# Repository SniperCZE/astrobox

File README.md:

# astrobox
DJ mixpult for amateur astronomy

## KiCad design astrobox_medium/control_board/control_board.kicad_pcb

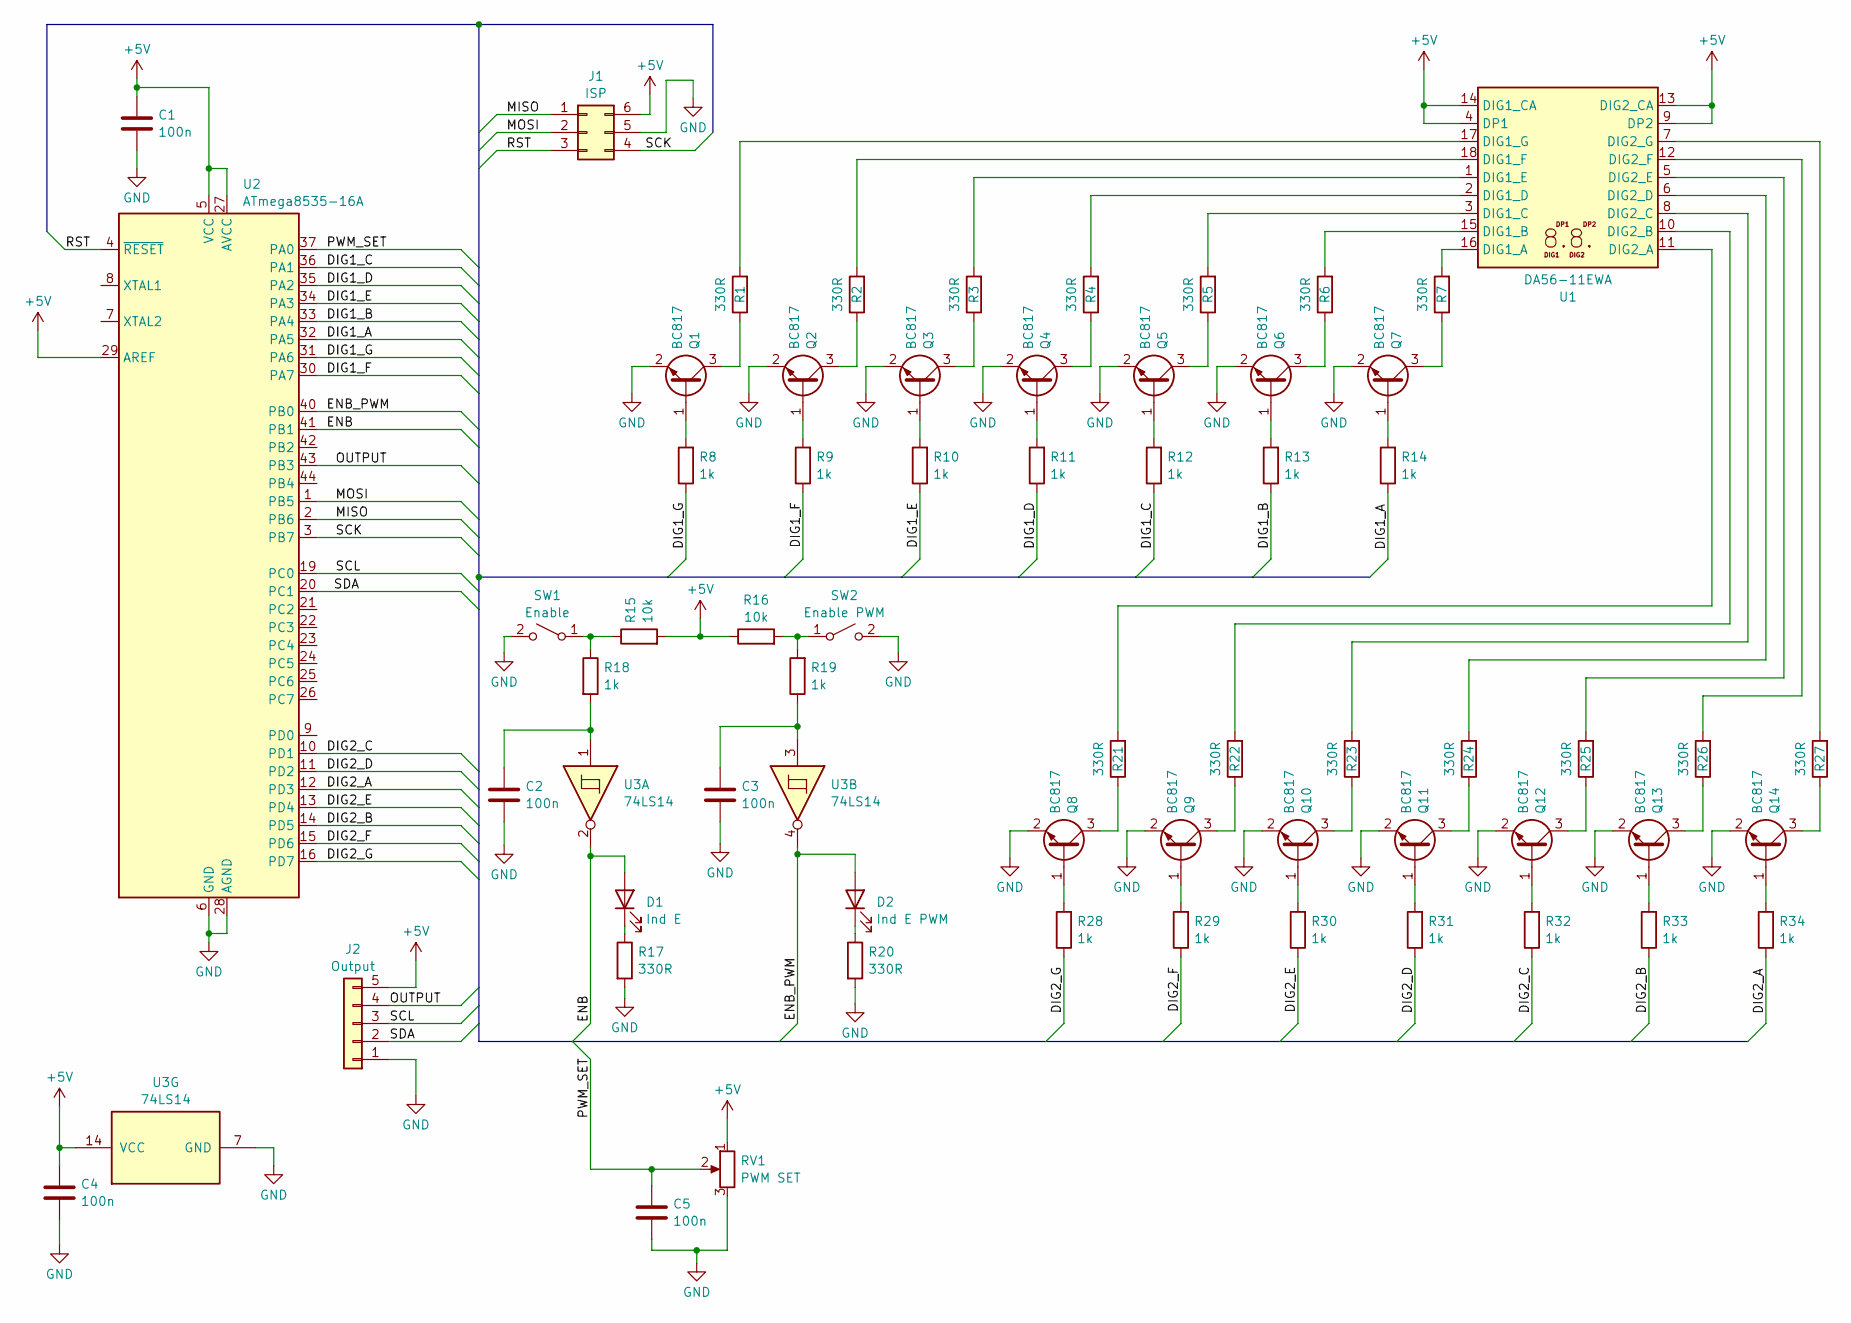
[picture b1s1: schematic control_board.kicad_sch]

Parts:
C1, C2, C3, C4, C5: 100n; C_1206_3216Metric_Pad1.33x1.80mm_HandSolder
D1: Ind E; LED_D5.0mm
D2: Ind E PWM; LED_D5.0mm
J1: ISP; PinHeader_2x03_P2.54mm_Vertical
J2: Output; SolderWire-1.5sqmm_1x05_P6mm_D1.7mm_OD3mm
Q1, Q2, Q3, Q4, Q5, Q6, Q7, Q8, Q9, Q10, Q11, Q12, Q13, Q14: BC817; SOT-23
R1, R2, R3, R4, R5, R6, R7, R17, R20, R21, R22, R23, R24, R25, R26, R27: 330R; R_1206_3216Metric_Pad1.30x1.75mm_HandSolder
R8, R9, R10, R11, R12, R13, R14, R18, R19, R28, R29, R30, R31, R32, R33, R34: 1k; R_1206_3216Metric_Pad1.30x1.75mm_HandSolder
R15, R16: 10k; R_1206_3216Metric_Pad1.30x1.75mm_HandSolder
RV1: PWM SET; SolderWire-1sqmm_1x03_P5.4mm_D1.4mm_OD2.7mm
SW1: Enable; SolderWire-1sqmm_1x02_P5.4mm_D1.4mm_OD2.7mm
SW2: Enable PWM; SolderWire-1sqmm_1x02_P5.4mm_D1.4mm_OD2.7mm
U1: DA56-11EWA; DA56-11SURKWA
U2: ATmega8535-16A; TQFP-44_10x10mm_P0.8mm
U3: 74LS14; SO-14_3.9x8.65mm_P1.27mm

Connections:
+5V: C1.1, C4.1, J1.6, J2.5, R15.2, R16.1, RV1.1, U1.4 (DP1), U1.9 (DP2), U1.13 (DIG2_CA), U1.14 (DIG1_CA), U2.5 (VCC), U2.17 (VCC), U2.27 (AVCC), U2.29 (AREF), U2.38 (VCC), U3.14 (VCC)
/DIG1_A: R14.1, U2.32 (PA5)
/DIG1_B: R13.1, U2.33 (PA4)
/DIG1_C: R12.1, U2.36 (PA1)
/DIG1_D: R11.1, U2.35 (PA2)
/DIG1_E: R10.1, U2.34 (PA3)
/DIG1_F: R9.1, U2.30 (PA7)
/DIG1_G: R8.1, U2.31 (PA6)
/DIG2_A: R34.1, U2.12 (PD3)
/DIG2_B: R33.1, U2.14 (PD5)
/DIG2_C: R32.1, U2.10 (PD1)
/DIG2_D: R31.1, U2.11 (PD2)
/DIG2_E: R30.1, U2.13 (PD4)
/DIG2_F: R29.1, U2.15 (PD6)
/DIG2_G: R28.1, U2.16 (PD7)
/ENB: D1.2 (A), U2.41 (PB1), U3.2
/ENB_PWM: D2.2 (A), U2.40 (PB0), U3.4
/MISO: J1.1, U2.2 (PB6)
/MOSI: J1.2, U2.1 (PB5)
/OUTPUT: J2.4, U2.43 (PB3)
/PWM_SET: C5.1, RV1.2, U2.37 (PA0)
/RST: J1.3, U2.4 (~RESET)
/SCK: J1.4, U2.3 (PB7)
/SCL: J2.3, U2.19 (PC0)
/SDA: J2.2, U2.20 (PC1)
GND: C1.2, C2.2, C3.2, C4.2, C5.2, J1.5, J2.1, Q1.2 (E), Q2.2 (E), Q3.2 (E), Q4.2 (E), Q5.2 (E), Q6.2 (E), Q7.2 (E), Q8.2 (E), Q9.2 (E), Q10.2 (E), Q11.2 (E), Q12.2 (E), Q13.2 (E), Q14.2 (E), R17.2, R20.2, RV1.3, SW1.2 (B), SW2.2 (B), U2.6 (GND), U2.18 (GND), U2.28 (AGND), U2.39 (GND), U3.7 (GND)
unnamed: C2.1, R18.2, U3.1
unnamed: C3.1, R19.1, U3.3
unnamed: D1.1 (K), R17.1
unnamed: D2.1 (K), R20.1
unnamed: Q1.1 (B), R8.2
unnamed: Q1.3 (C), R1.1
unnamed: Q2.1 (B), R9.2
unnamed: Q2.3 (C), R2.1
unnamed: Q3.1 (B), R10.2
unnamed: Q3.3 (C), R3.1
unnamed: Q4.1 (B), R11.2
unnamed: Q4.3 (C), R4.1
unnamed: Q5.1 (B), R12.2
unnamed: Q5.3 (C), R5.1
unnamed: Q6.1 (B), R13.2
unnamed: Q6.3 (C), R6.1
unnamed: Q7.1 (B), R14.2
unnamed: Q7.3 (C), R7.1
unnamed: Q8.1 (B), R28.2
unnamed: Q8.3 (C), R21.1
unnamed: Q9.1 (B), R29.2
unnamed: Q9.3 (C), R22.1
unnamed: Q10.1 (B), R30.2
unnamed: Q10.3 (C), R23.1
unnamed: Q11.1 (B), R31.2
unnamed: Q11.3 (C), R24.1
unnamed: Q12.1 (B), R32.2
unnamed: Q12.3 (C), R25.1
unnamed: Q13.1 (B), R33.2
unnamed: Q13.3 (C), R26.1
unnamed: Q14.1 (B), R34.2
unnamed: Q14.3 (C), R27.1
unnamed: R15.1, R18.1, SW1.1 (A)
unnamed: R16.2, R19.2, SW2.1 (A)
unnamed: R7.2, U1.16 (DIG1_A)
unnamed: R6.2, U1.15 (DIG1_B)
unnamed: R5.2, U1.3 (DIG1_C)
unnamed: R4.2, U1.2 (DIG1_D)
unnamed: R3.2, U1.1 (DIG1_E)
unnamed: R2.2, U1.18 (DIG1_F)
unnamed: R1.2, U1.17 (DIG1_G)
unnamed: R21.2, U1.11 (DIG2_A)
unnamed: R22.2, U1.10 (DIG2_B)
unnamed: R23.2, U1.8 (DIG2_C)
unnamed: R24.2, U1.6 (DIG2_D)
unnamed: R25.2, U1.5 (DIG2_E)
unnamed: R26.2, U1.12 (DIG2_F)
unnamed: R27.2, U1.7 (DIG2_G)

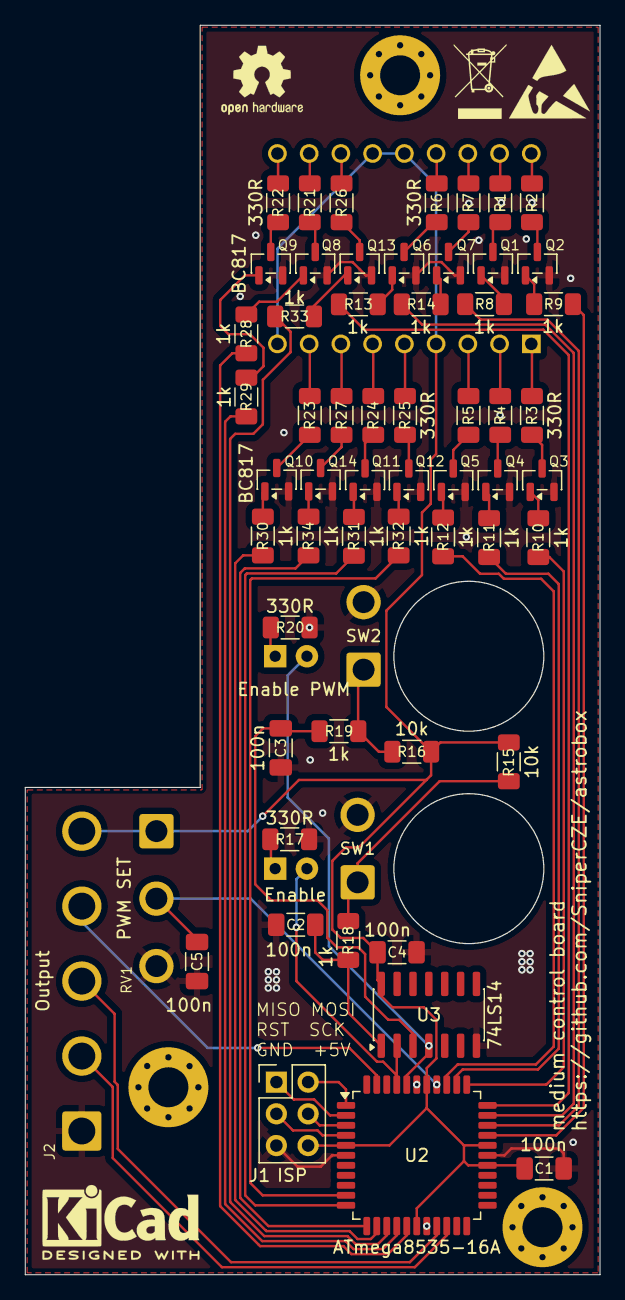
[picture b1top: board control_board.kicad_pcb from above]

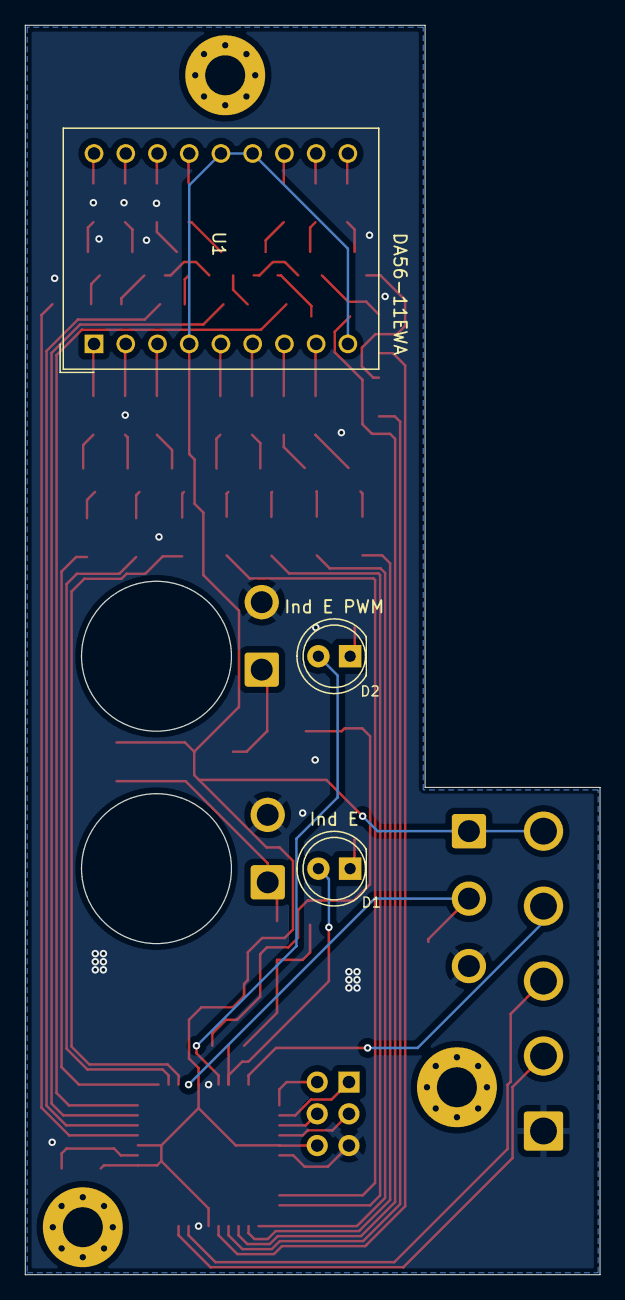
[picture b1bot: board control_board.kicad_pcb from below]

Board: 2 copper layers, 46.0 x 100.0 mm, 63 parts (3 on the bottom side), 74 nets.

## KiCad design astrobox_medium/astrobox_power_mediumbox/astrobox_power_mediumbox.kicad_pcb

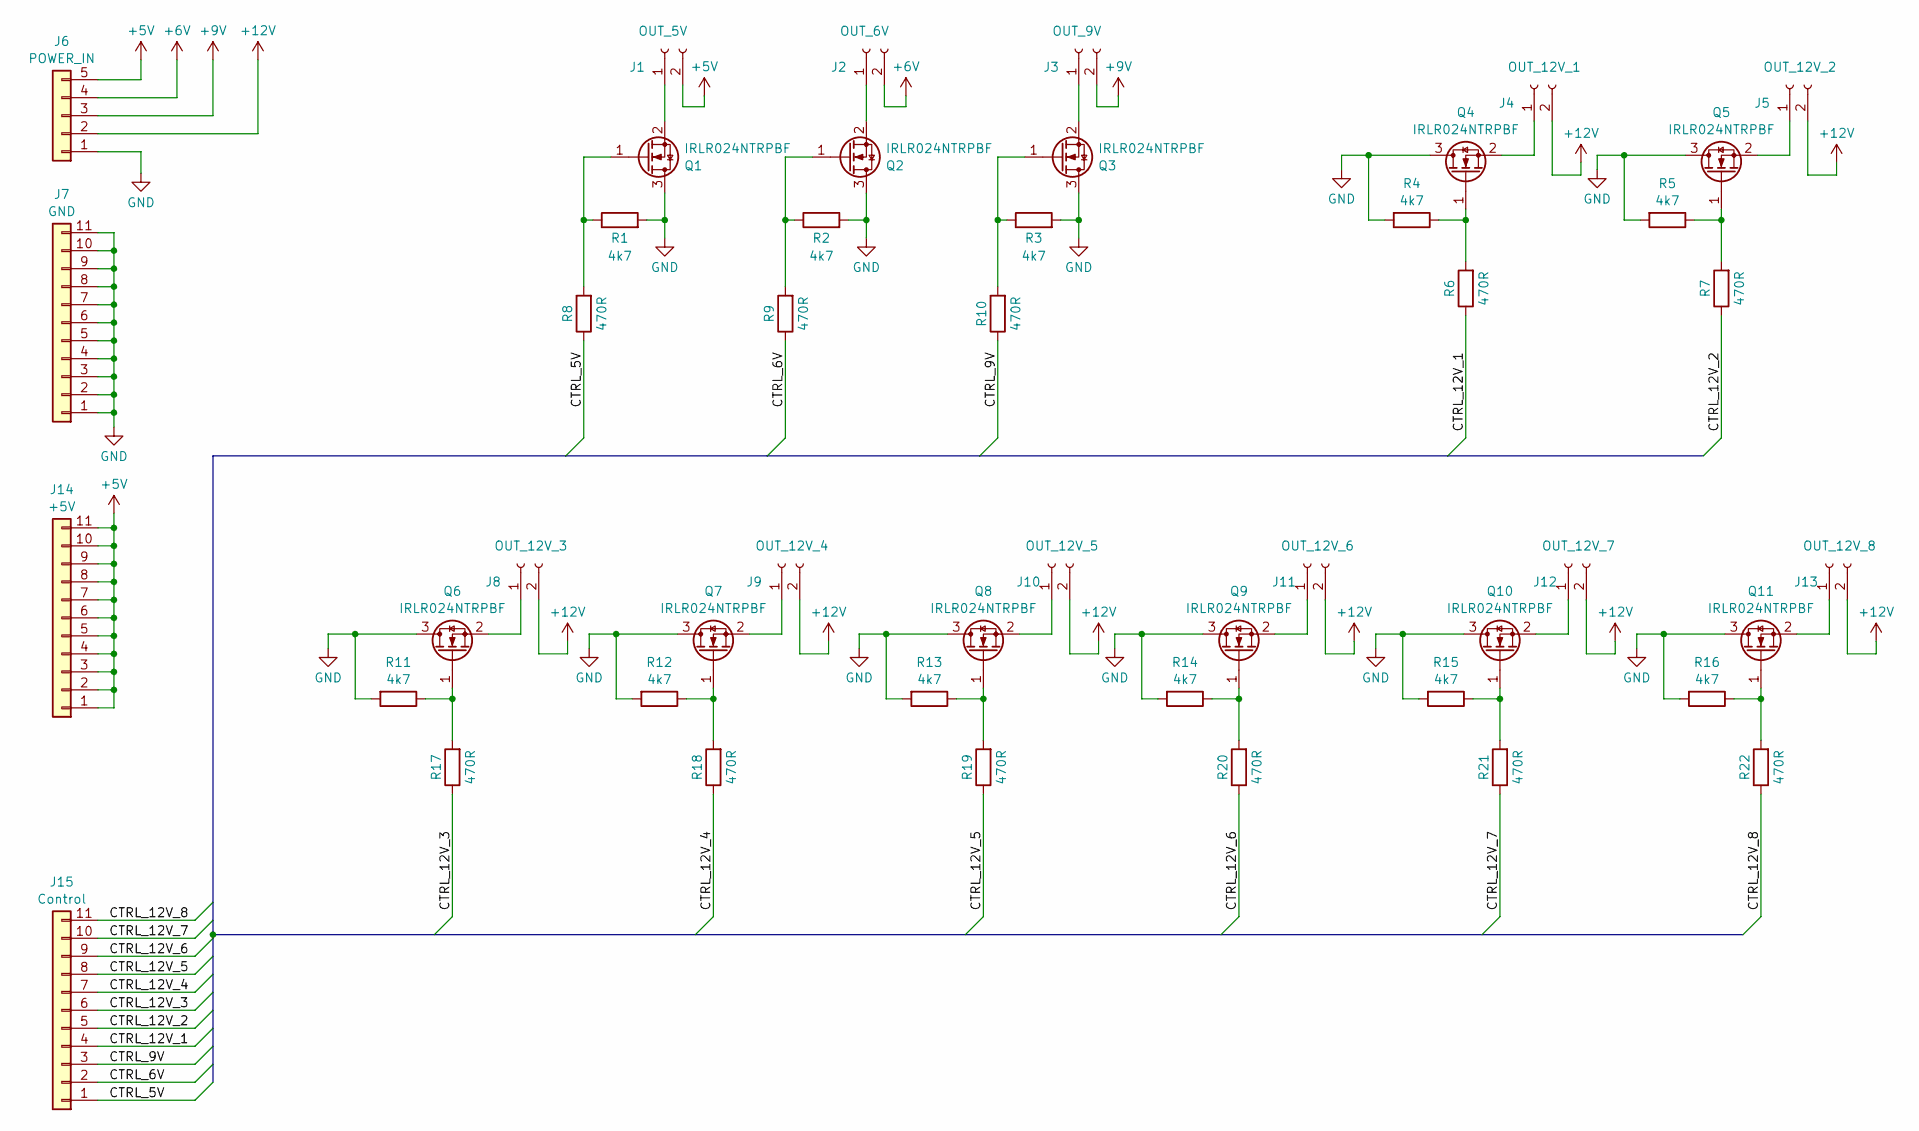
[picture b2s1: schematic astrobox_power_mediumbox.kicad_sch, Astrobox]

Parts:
J1: OUT_5V; SolderWire-1.5sqmm_1x02_P6mm_D1.7mm_OD3mm
J2: OUT_6V; SolderWire-1.5sqmm_1x02_P6mm_D1.7mm_OD3mm
J3: OUT_9V; SolderWire-1.5sqmm_1x02_P6mm_D1.7mm_OD3mm
J4: OUT_12V_1; SolderWire-1.5sqmm_1x02_P6mm_D1.7mm_OD3mm
J5: OUT_12V_2; SolderWire-1.5sqmm_1x02_P6mm_D1.7mm_OD3mm
J6: POWER_IN; SolderWire-1.5sqmm_1x05_P6mm_D1.7mm_OD3mm
J7: GND; PinHeader_1x11_P2.54mm_Vertical
J8: OUT_12V_3; SolderWire-1.5sqmm_1x02_P6mm_D1.7mm_OD3mm
J9: OUT_12V_4; SolderWire-1.5sqmm_1x02_P6mm_D1.7mm_OD3mm
J10: OUT_12V_5; SolderWire-1.5sqmm_1x02_P6mm_D1.7mm_OD3mm
J11: OUT_12V_6; SolderWire-1.5sqmm_1x02_P6mm_D1.7mm_OD3mm
J12: OUT_12V_7; SolderWire-1.5sqmm_1x02_P6mm_D1.7mm_OD3mm
J13: OUT_12V_8; SolderWire-1.5sqmm_1x02_P6mm_D1.7mm_OD3mm
J14: +5V; PinHeader_1x11_P2.54mm_Vertical
J15: Control; PinHeader_1x11_P2.54mm_Vertical
Q1, Q2, Q3, Q4, Q5, Q6, Q7, Q8, Q9, Q10, Q11: IRLR024NTRPBF; TO-252-3_TabPin2
R1, R2, R3, R4, R5, R11, R12, R13, R14, R15, R16: 4k7; R_1206_3216Metric_Pad1.30x1.75mm_HandSolder
R6, R7, R8, R9, R10, R17, R18, R19, R20, R21, R22: 470R; R_1206_3216Metric_Pad1.30x1.75mm_HandSolder

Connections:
+5V: J1.2, J6.5, J14.1, J14.2, J14.3, J14.4, J14.5, J14.6, J14.7, J14.8, J14.9, J14.10, J14.11
+6V: J2.2, J6.4
+9V: J3.2, J6.3
+12V: J4.2, J5.2, J6.2, J8.2, J9.2, J10.2, J11.2, J12.2, J13.2
/CTRL_5V: J15.1, R8.1
/CTRL_6V: J15.2, R9.1
/CTRL_9V: J15.3, R10.1
/CTRL_12V_1: J15.4, R6.1
/CTRL_12V_2: J15.5, R7.1
/CTRL_12V_3: J15.6, R17.1
/CTRL_12V_4: J15.7, R18.1
/CTRL_12V_5: J15.8, R19.1
/CTRL_12V_6: J15.9, R20.1
/CTRL_12V_7: J15.10, R21.1
/CTRL_12V_8: J15.11, R22.1
GND: J6.1, J7.1, J7.2, J7.3, J7.4, J7.5, J7.6, J7.7, J7.8, J7.9, J7.10, J7.11, Q1.3 (D), Q2.3 (D), Q3.3 (D), Q4.3 (D), Q5.3 (D), Q6.3 (D), Q7.3 (D), Q8.3 (D), Q9.3 (D), Q10.3 (D), Q11.3 (D), R1.2, R2.2, R3.2, R4.2, R5.2, R11.2, R12.2, R13.2, R14.2, R15.2, R16.2
unnamed: J1.1, Q1.2 (S)
unnamed: J2.1, Q2.2 (S)
unnamed: J3.1, Q3.2 (S)
unnamed: J4.1, Q4.2 (S)
unnamed: J5.1, Q5.2 (S)
unnamed: J8.1, Q6.2 (S)
unnamed: J9.1, Q7.2 (S)
unnamed: J10.1, Q8.2 (S)
unnamed: J11.1, Q9.2 (S)
unnamed: J12.1, Q10.2 (S)
unnamed: J13.1, Q11.2 (S)
unnamed: Q1.1 (G), R1.1, R8.2
unnamed: Q2.1 (G), R2.1, R9.2
unnamed: Q3.1 (G), R3.1, R10.2
unnamed: Q4.1 (G), R4.1, R6.2
unnamed: Q5.1 (G), R5.1, R7.2
unnamed: Q6.1 (G), R11.1, R17.2
unnamed: Q7.1 (G), R12.1, R18.2
unnamed: Q8.1 (G), R13.1, R19.2
unnamed: Q9.1 (G), R14.1, R20.2
unnamed: Q10.1 (G), R15.1, R21.2
unnamed: Q11.1 (G), R16.1, R22.2

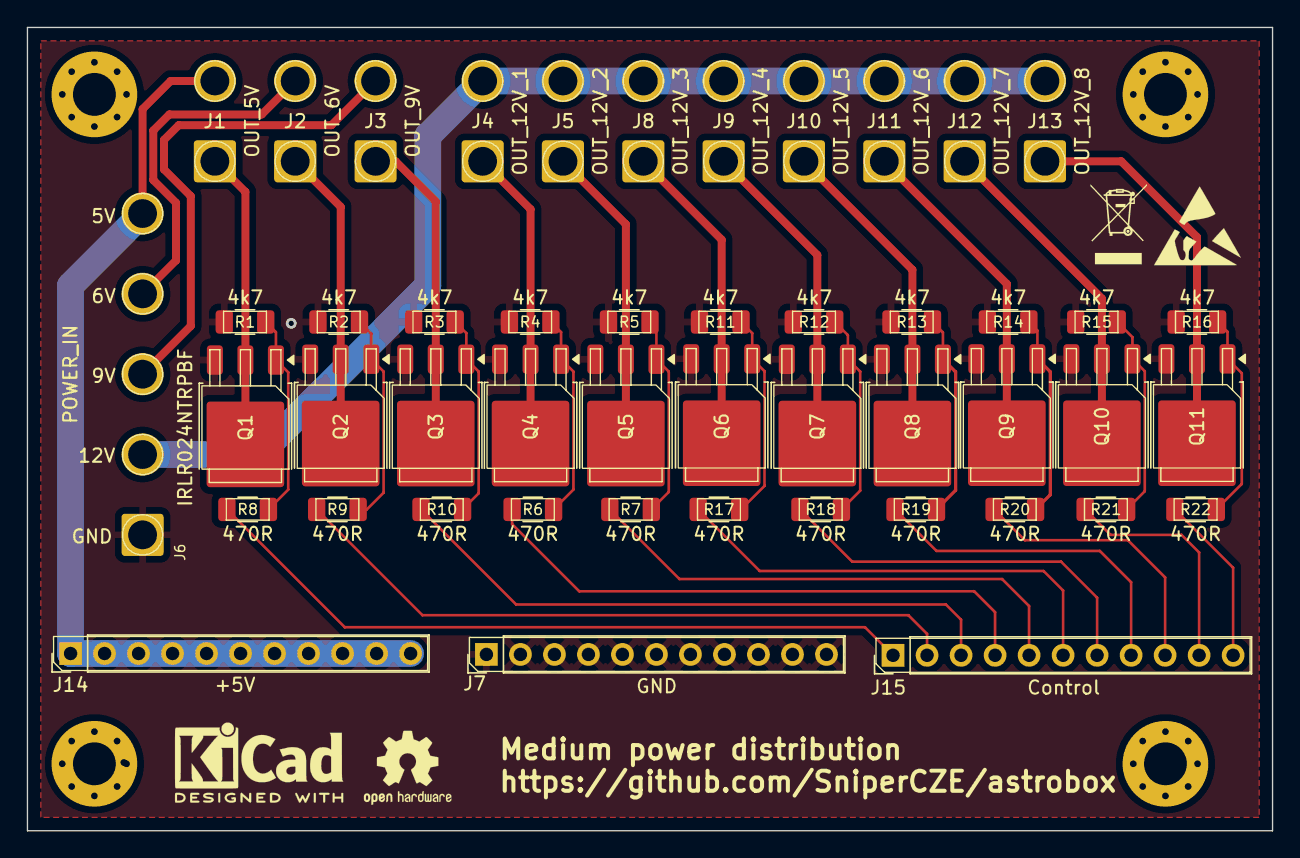
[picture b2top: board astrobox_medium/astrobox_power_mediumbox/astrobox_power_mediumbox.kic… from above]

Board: 2 copper layers, 93.0 x 60.0 mm, 48 parts (0 on the bottom side), 38 nets.

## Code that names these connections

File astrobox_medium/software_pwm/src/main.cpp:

/**
 *
 * Ovladani napajeciho modulu Astroboxu.
 *
 * Funkce:
 * - Cteni potenciometru na PA0 (ADC)
 * - PWM vystup na PB3 (Timer0)
 * - Ovladani vystupu pomoci PB0 (PWM enable) a PB1 (Output enable)
 * - Zobrazeni % (0-99) na 2x 7-seg displeji (PORTA - desitky, PORTD - jednotky)
 *
 * @author: Ondrej Flidr <ondrej.flidr@seznam.cz>
 * @version: 0.1
 * @date: 21/11/2025
 *
 */

#ifndef F_CPU
#define F_CPU 1000000UL // 1 MHz
#endif

#include <avr/io.h>
#include <util/delay.h>

// Definice pinu
#define PIN_PWM_ENABLE  PB0
#define PIN_OUTPUT_EN   PB1
#define PIN_PWM_OUT     PB3

// Makra pro cteni vstupu
#define IS_PWM_ENABLE_LOW()   bit_is_clear(PINB, PIN_PWM_ENABLE)
#define IS_PWM_ENABLE_HIGH()  bit_is_set(PINB, PIN_PWM_ENABLE)
#define IS_OUTPUT_EN_LOW()    bit_is_clear(PINB, PIN_OUTPUT_EN)
#define IS_OUTPUT_EN_HIGH()   bit_is_set(PINB, PIN_OUTPUT_EN)

/**
 * Mapovani segmentu na piny
 * Standardni 7-seg:      A, B, C, D, E, F, G
 * Index bitu (standard): 0, 1, 2, 3, 4, 5, 6
 *
 * Desitky (PORTA):
 * A->PA5, B->PA4, C->PA1, D->PA2, E->PA3, F->PA7, G->PA6
 *
 * Jednotky (PORTD):
 * A->PD7, B->PD6, C->PD4, D->PD2, E->PD1, F->PD5, G->PD3
 */

// Standardni definice cislic 0-9 (abcdefg)
// 0=0x3F, 1=0x06, 2=0x5B, 3=0x4F, 4=0x66, 5=0x6D, 6=0x7D, 7=0x07, 8=0x7F, 9=0x6F
const uint8_t digits_standard[] = {
    0x3F, 0x06, 0x5B, 0x4F, 0x66, 0x6D, 0x7D, 0x07, 0x7F, 0x6F
};

// Prevodni tabulky (vypoctene rucne pro optimalizaci)
// PORTA (Tens) - PA0 je input (ADC), takze maskujeme jen bity 1-7
const uint8_t segment_map_tens[] = {
    // 0: ABCDEF -> 5,4,1,2,3,7 -> 0b10111110 = 0xBE
    0xBE,
    // 1: BC -> 4,1 -> 0b00010010 = 0x12
    0x12,
    // 2: ABDEG -> 5,4,2,3,6 -> 0b01111100 = 0x7C
    0x7C,
    // 3: ABCDG -> 5,4,1,2,6 -> 0b01110110 = 0x76
    0x76,
    // 4: BCFG -> 4,1,7,6 -> 0b11010010 = 0xD2
    0xD2,
    // 5: ACDFG -> 5,1,2,7,6 -> 0b11100110 = 0xE6
    0xE6,
    // 6: ACDEFG -> 5,1,2,3,7,6 -> 0b11101110 = 0xEE
    0xEE,
    // 7: ABC -> 5,4,1 -> 0b00110010 = 0x32
    0x32,
    // 8: ABCDEFG -> vse krome 0 -> 0b11111110 = 0xFE
    0xFE,
    // 9: ABCDFG -> 5,4,1,2,7,6 -> 0b11110110 = 0xF6
    0xF6
};

// PORTD (Units) - PD0 nepripojen
const uint8_t segment_map_units[] = {
    // 0: ABCDEF -> 7,6,5,4,2,1 -> 0b11110110 = 0xF6
    0xF6,
    // 1: BC -> 6,4 -> 0b01010000 = 0x50
    0x50,
    // 2: ABDEG -> 7,6,2,1,3 -> 0b11001110 = 0xCE
    0xCE,
    // 3: ABCDG -> 7,6,4,2,3 -> 0b11011100 = 0xDC
    0xDC,
    // 4: BCFG -> 6,4,5,3 -> 0b01111000 = 0x78
    0x78,
    // 5: ACDFG -> 7,4,2,5,3 -> 0b10111100 = 0xBC
    0xBC,
    // 6: ACDEFG -> 7,4,2,1,5,3 -> 0b10111110 = 0xBE
    0xBE,
    // 7: ABC -> 7,6,4 -> 0b11010000 = 0xD0
    0xD0,
    // 8: ABCDEFG -> vse krome 0 -> 0b11111110 = 0xFE
    0xFE,
    // 9: ABCDFG -> 7,6,4,2,5,3 -> 0b11111100 = 0xFC
    0xFC
};

void adc_init() {
    // ADMUX: REFS0=0, REFS1=0 (AREF, Internal Vref turned off)
    //        MUX=00000 (ADC0/PA0)
    ADMUX = 0x00;

    // ADCSRA: ADEN=1 (Enable), ADPS=011 (Prescaler 8 -> 1MHz/8 = 125kHz)
    ADCSRA = (1 << ADEN) | (1 << ADPS1) | (1 << ADPS0);
}

uint16_t adc_read() {
    // Start conversion
    ADCSRA |= (1 << ADSC);
    // Wait for conversion to complete
    while (ADCSRA & (1 << ADSC));
    return ADC;
}

void timer0_init() {
    // Fast PWM mode (WGM01 | WGM00)
    // Non-inverting mode (COM01=1, COM00=0) - Clear OC0 on match, set at BOTTOM
    // Clock: No prescaling (CS00=1) -> 1MHz PWM freq ~3.9kHz
    // Inicialne odpojime OC0 od pinu (bude se ovladat v loopu)
    TCCR0 = (1 << WGM00) | (1 << WGM01) | (1 << CS00);
    DDRB |= (1 << PIN_PWM_OUT); // PB3 jako vystup
}

void update_display(uint8_t percent) {
    if (percent > 99) percent = 99;

    uint8_t tens = percent / 10;
    uint8_t units = percent % 10;

    // PORTA: Zachovat PA0 (ADC input), prepsat PA1-PA7
    // PORTA input buffer (PIN A) by nemel byt ovlivnen, zapisujeme do LAT (PORT)
    // Ale PA0 je input bez pullupu (reseno v DDR), takze zapis 0 na PA0 je OK.
    // Pro jistotu cteme aktualni stav PORTA, zachovame bit 0 a zbytek pre napiseme.
    uint8_t current_porta = PORTA & 0x01;
    PORTA = current_porta | (segment_map_tens[tens] & 0xFE);

    // PORTD: PD0 nepripojen, muzeme prepsat, ale slusnost je zachovat
    uint8_t current_portd = PORTD & 0x01;
    PORTD = current_portd | (segment_map_units[units] & 0xFE);
}

int main(void) {
    // 1. Nastaveni portu
    // PORTA: PA0 Input (ADC), PA1-PA7 Output (Display Tens)
    DDRA = 0xFE; // 1111 1110
    PORTA = 0x00; // Vse LOW

    // PORTD: PD0 Input/Unused, PD1-PD7 Output (Display Units)
    DDRD = 0xFE; // 1111 1110
    PORTD = 0x00; // Vse LOW

    // PORTB: PB0, PB1 Input, PB3 Output (PWM)
    DDRB = (1 << PB3); // Ostatni jsou input (0)
    // Volitelne: Zapnout pull-up na vstupech, pokud nejsou externi?
    // Zadala se "Aktivace PWM", "Aktivace outputu", predpokladam aktivni logiku zvenku.
    // Necham bez pull-upu (High-Z), pokud neni specifikovano jinak.

    // 2. Inicializace periferii
    adc_init();
    timer0_init();

    uint16_t adc_val = 0;
    uint8_t percent = 0;
    uint8_t pwm_val = 0;

    while (1) {
        // Cteni ADC
        adc_val = adc_read(); // 0 - 1023

        // Prepocet
        // Procenta: (adc * 100) / 1024 ... zjednodusene adc/10.23
        // Pro lepsi presnost: (adc * 100) >> 10 je cca spravne, ale max 102300/1024 = 99.9
        percent = (adc_val * 100UL) / 1024UL;
        if (percent > 99) percent = 99;

        // PWM duty: mapovani 0-1023 na 0-255 -> deleno 4
        pwm_val = adc_val >> 2;

        // Aktualizace displeje
        update_display(percent);

        //// Logika rizeni vystupu PB3
        //if (IS_OUTPUT_EN_LOW()) {
        //    // PB1 == LOW -> Vystup vzdy LOW (Safety OFF)
        //    // Odpojit Timer od pinu
        //    TCCR0 &= ~(1 << COM01);
        //    // Nastavit pin LOW
        //    PORTB &= ~(1 << PIN_PWM_OUT);
        //}
        //else {
        //    // PB1 == HIGH
        //    if (IS_PWM_ENABLE_LOW()) {
        //        // PB0 == LOW -> Vystup trvale HIGH (Full ON)
        //        // Odpojit Timer od pinu
        //        TCCR0 &= ~(1 << COM01);
        //        // Nastavit pin HIGH
        //        PORTB |= (1 << PIN_PWM_OUT);
        //    }
        //    else {
        //        // PB1 == HIGH && PB0 == HIGH -> PWM Signal
        //        // Nastavit stridu
        //        OCR0 = pwm_val;
        //        // Pripojit Timer k pinu (Clear OC0 on Compare Match, Set at BOTTOM)
        //        TCCR0 |= (1 << COM01);
        //    }
        //}

        _delay_ms(10); // Maly delay pro stabilitu
    }
}

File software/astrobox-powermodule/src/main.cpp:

/**
 *
 * Ovladani napajeciho modulu Astroboxu.
 * 
 * Procesor napajecího modulu Astroboxu má za úkol 
 * spustit napájení do dalších částí a zároveň přes
 * modul DHT11 hlídat vnitřní prostředí - Rh a T.
 * Pokud hodnoty teploty nebo Rh dosáhnou limitních
 * hodnot, spustí přes PWM řízení větráku.
 * Procesor se chová jako I2C slave a je možné z něj
 * vyčíst informace o aktuální T a Rh.
 *
 * Konfigurace pinů:
 *         ______
 * PB5 - 1 |    | 8 - VCC
 * PB3 - 2 |    | 7 - PB2
 * PB4 - 3 |    | 6 - PB1
 * GND - 4 |    | 5 - PB0
 *         ------
 * 
 * VCC, GND = Napájení
 * PB0 - I2C SDA
 * PB1 - Aktivace napájení v celém obvodu
 * PB2 - I2C SCL
 * PB3 - Signalizace přiliš vysoké Rh
 * PB4 - PWM ovládání větráčku
 * PB5 - Reset / Data z DHT11
 *
 * @author: Ondrej Flidr <ondrej.flidr@seznam.cz>
 * @version: 0.1
 * @date: 26/05/2024
 *
 */

#define F_CPU 1000000 // frekvence CPU na 1MHz (default, nepouzivam krystal)
#define I2C_ADDRESS 0x51 // I2C adresa na ktere posloucham
#define WANT_RELHUM 0x1 // Master pozaduje udaje o vlhkosti
#define WANT_TEMPER 0x2 // Master pozaduje udaje o teplote
#define DHT_TYPE DHT11 // Typ DHT senzoru
#define DHT_PIN 5 // Pin DHT senzoru

#include <avr/io.h>
#include <util/delay.h>
#include <avr/interrupt.h>
#include <TinyWireS.h>
#include <TinyDHT.h>

int8_t requestType=0;
int8_t humidity;
int16_t temperature;

void i2c_request(void)
{
  if (requestType == WANT_RELHUM) {
    TinyWireS.send(0x58);
  } else if (requestType == WANT_TEMPER) {
    TinyWireS.send(0x47);
  }
}

void i2c_receive(uint8_t data)
{
  requestType = data;
}

int main(void)
{

  DDRB = 0b00001010;
  
  // Po zapnuti eletkriny sepnu relatka
  PORTB = 0b00000010;
  _delay_ms(200);

  TinyWireS.begin(I2C_ADDRESS);
  TinyWireS.onReceive(i2c_receive);
  TinyWireS.onRequest(i2c_request);

  DHT dht(DHT_PIN, DHT_TYPE);
  dht.begin();

  _delay_ms(500);


	while(1) {

    int8_t h = dht.readHumidity();
    int16_t t = dht.readTemperature();

    _delay_ms(500);

	}

}
